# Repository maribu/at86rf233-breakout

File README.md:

AT86RF233 Breakout
==================

This Repository contains an AT86RF233 breakout board that uses the basic
application schematic given in Section 5.1 "Basic Application Schematic" on
page 15 of the AT86RF233 datasheet (07/2014), with two differences:

1. The optional clock output is omitted
2. The 2.4 gigahertz antenna circuit from the [AT86RF215-XPRO](https://static5.arrow.com/pdfs/2015/6/30/10/21/54/282/atm_/manual/251atreb215-xpro_design_documentation.pdf)
   is used instead the on given in the AT86RF233 basic application schematic.
   The shielding used in the AT86RF215-XPRO is omitted.

This board is intentionally pin compatible with the openlabs.co RPI 802.15.4
radio - but not based on their design.

WARNING
=======

1. It is highly recommended to not order PCBs based on this design as of now.
   This design has never been tested.
2. There is absolutely no warranty.
3. The AT86RF233 chip, the 2 x 6 female pin header, and the SMA connector are
   note included in the generated BOM an need to be hand soldered.

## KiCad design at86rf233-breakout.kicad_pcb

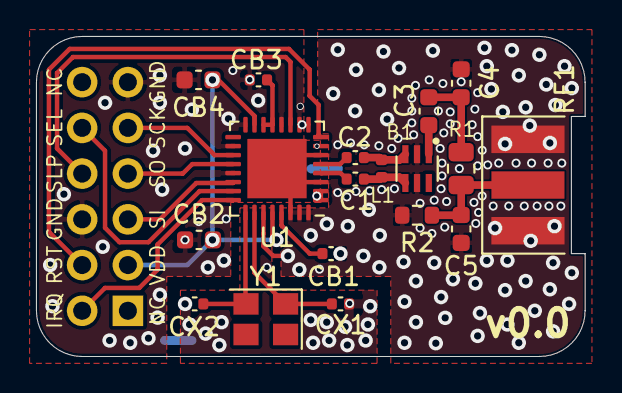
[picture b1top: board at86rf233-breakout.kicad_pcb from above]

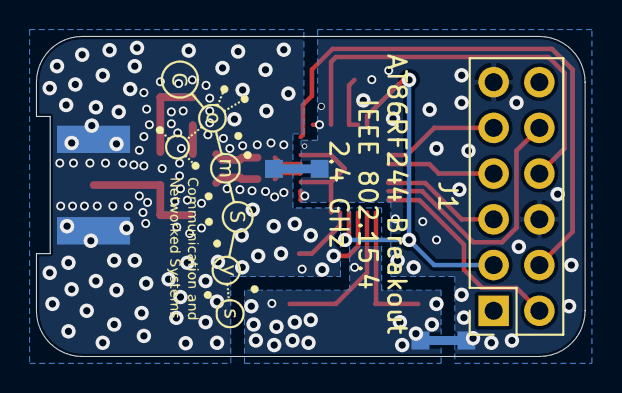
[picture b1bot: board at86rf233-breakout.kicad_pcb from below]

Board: 2 copper layers, 30.5 x 17.8 mm, 21 parts (3 on the bottom side), 22 nets.

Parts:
B1: Balun_HHM1711D1; TDK-HHM1711D1
C1, C2: 1.8 pF; C_0402_1005Metric
C3: 0.8 pF; C_0603_1608Metric
C4, C5: 1.2 pF; C_0603_1608Metric
CB1, CB3: 100 nF; C_0402_1005Metric
CB2, CB4: 1 µF; C_0603_1608Metric
CX1, CX2: 12 pF; C_0402_1005Metric
J1: RPi Header; PinSocket_2x06_P2.54mm_Vertical
L1: 5.6 nH; L_0402_1005Metric
R1: 0 Ω; R_0805_2012Metric
R2: 10 kΩ; R_0603_1608Metric
R3, R4: 0 Ω; R0
RF1: ANT; Connector-SMA
U1: AT86RF233-ZU; QFN-32-1EP_5x5mm_P0.5mm_EP3.3x3.3mm
Y1: 16 MHz; Crystal_SMD_TXC_7M-4Pin_3.2x2.5mm

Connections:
/ANT: C5.1, R1.2, R2.1, RF1.1
/ANT': C3.2, C4.1, R1.1
/ANT'': B1.1, C3.1
/AVDD: CB1.1, U1.29
/DVDD: CB3.1, U1.13, U1.14
/IRQ: J1.2, U1.24
/MISO: J1.7, U1.20
/MOSI: J1.5, U1.22
/RFN: C2.2, U1.5
/RFN': B1.3, C2.1, L1.2
/RFP: C1.2, U1.4
/RFP': B1.4, C1.1, L1.1
/RST: J1.4, U1.8
/SCLK: J1.9, U1.19
/SEL: J1.10, U1.23
/SLP_TR: J1.8, U1.11
/XTAL1: CX1.2, U1.26, Y1.1
/XTAL2: CX2.2, U1.25, Y1.2
GND: CB2.1, CB3.2, CB4.1, J1.6, J1.11, R3.2, R4.2, U1.1, U1.2, U1.7, U1.9, U1.10, U1.12, U1.16, U1.18, U1.21
GND2: CX1.1, CX2.1, R3.1
GNDA: B1.2, B1.5, C4.2, C5.2, CB1.2, R2.2, R4.1, RF1.2, U1.3, U1.6, U1.27, U1.30, U1.31, U1.32, U1.33
VDD: CB2.2, CB4.2, J1.3, U1.15, U1.28
